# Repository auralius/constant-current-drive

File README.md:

# constant-current-drive

This is a simple circuit for sending constant current to a load, even if the load is varying over time.

## Single-directional drive

### Schematic
This picture below shows the current-sink configuration. In the **ltspice folder**, the more common current-source configuration is used for simulations.  

Note: replace IRF540 with IRFZ44N   

### PCB

## Two-directional drive

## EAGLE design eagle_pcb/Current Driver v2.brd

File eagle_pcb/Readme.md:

Software: Eagle 9.6.2

There is a ZIP file containing Gerber files that have been sent for fabrication successfully.

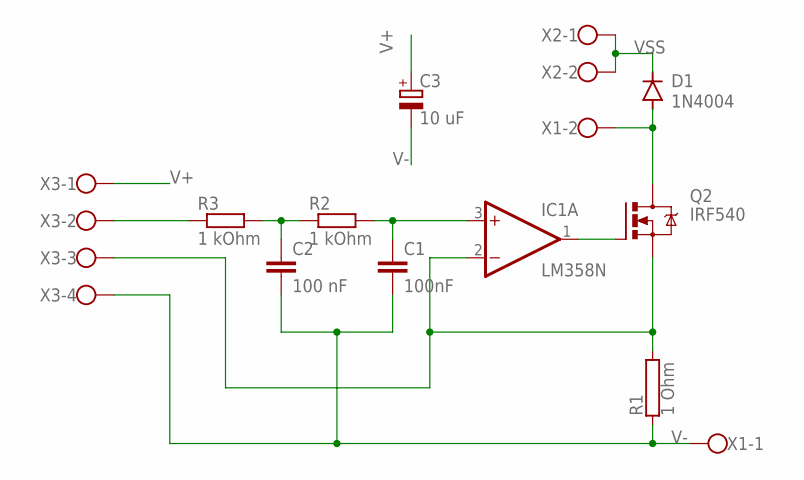
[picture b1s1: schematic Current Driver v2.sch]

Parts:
C1: 100nF; C050-030X075
C2: 100 nF; C050-030X075
C3: 10 uF; E2,5-6E
D1: 1N4004; DO41-10
IC1: LM358N; DIL08
Q2: IRF540; TO220BV
R1: 1 Ohm; AC05
R2, R3: 1 kOhm; 0204/7
X1, X2: W237-102
X3: W237-4

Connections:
unnamed: IC1.1 (OUT), Q2.G
unnamed: D1.A, Q2.D, X1.2
unnamed: C2.1, R2.1, R3.2
unnamed: C1.1, IC1.3 (+IN), R2.2
unnamed: R3.1, X3.2
unnamed: IC1.2 (-IN), Q2.S, R1.2, X3.3
V+: C3.+, IC1.8 (V+), X3.1
V-: C1.2, C2.2, C3.-, IC1.4 (V-), R1.1, X1.1, X3.4
VSS: D1.C, X2.1, X2.2

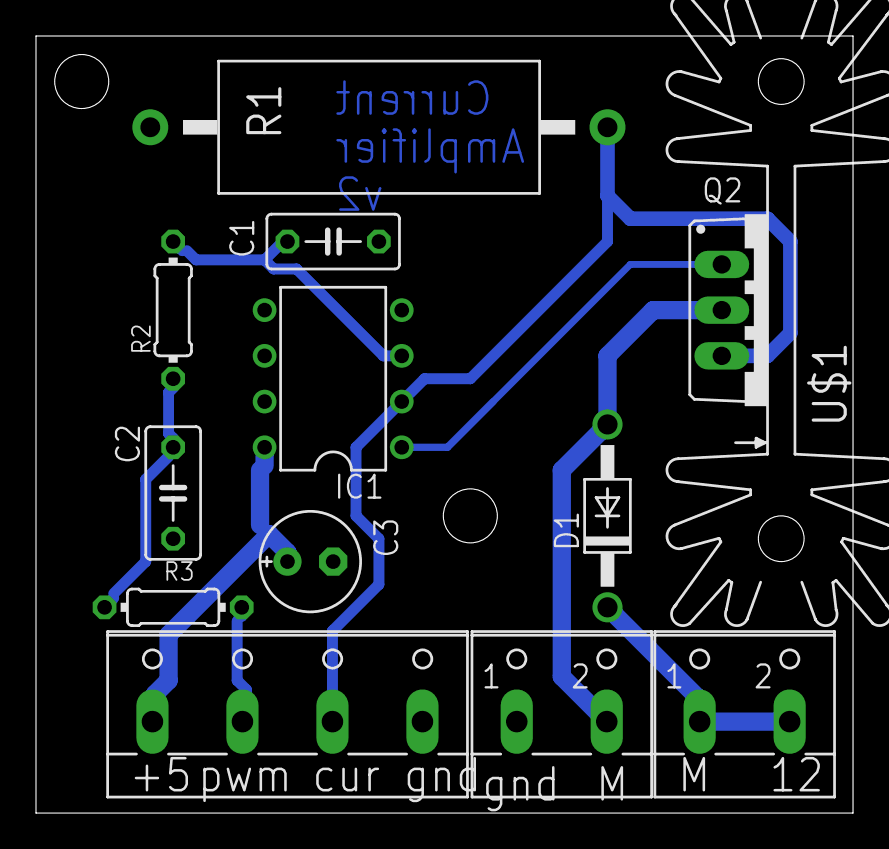
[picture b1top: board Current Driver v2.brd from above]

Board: 2 copper layers, 45.4 x 43.2 mm, 13 parts (0 on the bottom side), 9 nets.

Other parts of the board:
U$1: SK104

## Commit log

2022-05-07 Add the schematic picture
2022-05-13 Add an ltspice simulation file
2022-05-17 Add ltspice simulation for all cases.
2022-06-16 Now using TL431
2025-12-05 Bidirectional drive with LM675
2025-12-05 Update README with drive configurations and schematics
    Added sections for single-directional and two-directional drive with schematics.
2025-12-05 Dual rail supply follows official datasheet.
2025-12-05 Add TL431 ltspice model
